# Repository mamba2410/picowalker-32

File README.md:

# picowalker-32

Thsi repo contains all the designs, schematics, pcb layouts and code for the *picowalker-32* project.

The *picowalker-32* is a modern, open source and faithful recreation of the *Pokewalker* from *Pokemon HeartGold/SoulSilver*.
The goal is to have a device that fully mimics the features and functionality of a *Pokewalker*, except made with modern 
features such as a rechargeable battery, colour screen and an additional flash memory chip to store more data.

The *picowalker-32* is based on the STM32U535 chip, which has far more ram, flash and computing capabilities than the original
processor. Most importantly, its available to purchase, even in small quantities.
Due to the lack of options for screens and batteries, the *picowalker-32* is slightly larger than the original *Pokewalker*.

The software in this repo is designed to be enough to run the [picowalker-core]() code to fully simulate a *Pokewalker*,
however, theres no reason that other software can't be run on it!

The name *picowalker-32* comes from the original *picowalker* concept, a [mintyPi](https://sudomod.com/mintypi-v3-5/) inspired
pokewalker, based on the [Raspberry Pi Pico](https://www.raspberrypi.com/products/raspberry-pi-pico/), hence the *pico* in the name.
The project later evolved into a custom-PCB solution using an STM32 controller for lower power draw. Hence the *-32* suffix.

## What's in this repo

- Design files for the schematics and PCB layout, drawn in KiCAD 7.
- STM32CubeMX configuration for the STM32U545 chip used in the design.
- STM32 code using the STM32 HAL for the drivers and dependencies that the [picowalker-core](https://github.com/mamba2410/picowalker-core) needs to function.
- Developer notes and a bill of materials used in testing.
- Other, miscellaneous notes related to the *picowalker-32* project.

## The state of the project

Currently, the project is in active development.
There are schematics, the start of some code and materials that have been picked out.
The project is being prototyped on a breadboard using the *NUCLEO-U545RE* development board and other
breakout boards for fast prototyping.

Left to do:

- Finish the schematics (power delivery, other checks).
- Finish the driver for the screen.
- Start drivers for the IR, accelerometer, eeprom, flash memory, sound, buttons and others.
- Route the PCB (either a test PCB or directly onto the final form factor).
- Manufacture and test the PCB and iterate on it.

## Development and Contribution

If you want to help develop this project, make sure to read the [development document](./development.md) for instructions 
on how to recreate the project at home.

I encourage you to come join the [Discord](https://discord.gg/dVVnM6f5tP)! This is where most of the discussion happens about the project.
There's also other stuff related to the *Pokewalker* including reverse enginnering and hacking it.

Thanks to all the contributors who have helped out a lot, especially

- Kamp, for doing all the CAD work for the shells, picking out components like the screen and battery (which were really hard to find!) and others.
- Zenith, for help with sprites and images and even recreating most of the coloured ones to work on the walker.
- PoroCYon, for help with schematics, electrical questions and picking a suitable MCU.

## Licensing

I'm not sure about the license, I want this project to be as open and accessible as possible.

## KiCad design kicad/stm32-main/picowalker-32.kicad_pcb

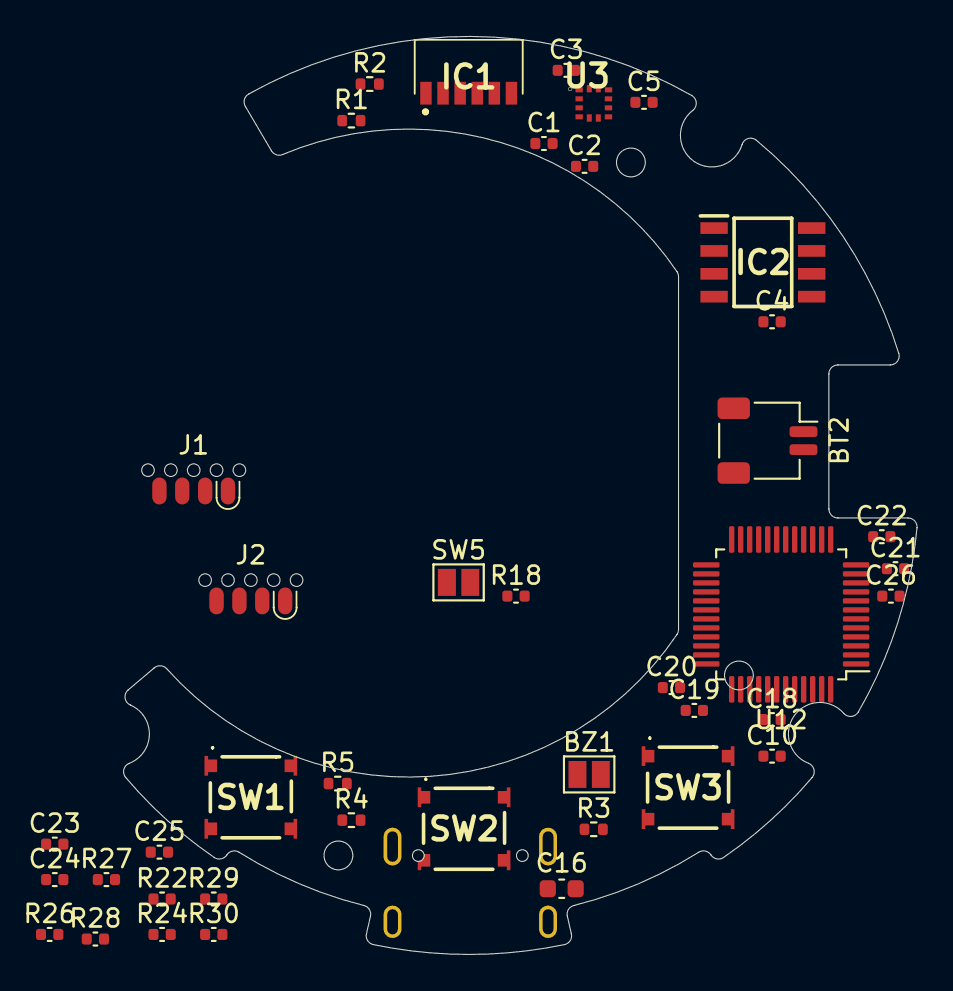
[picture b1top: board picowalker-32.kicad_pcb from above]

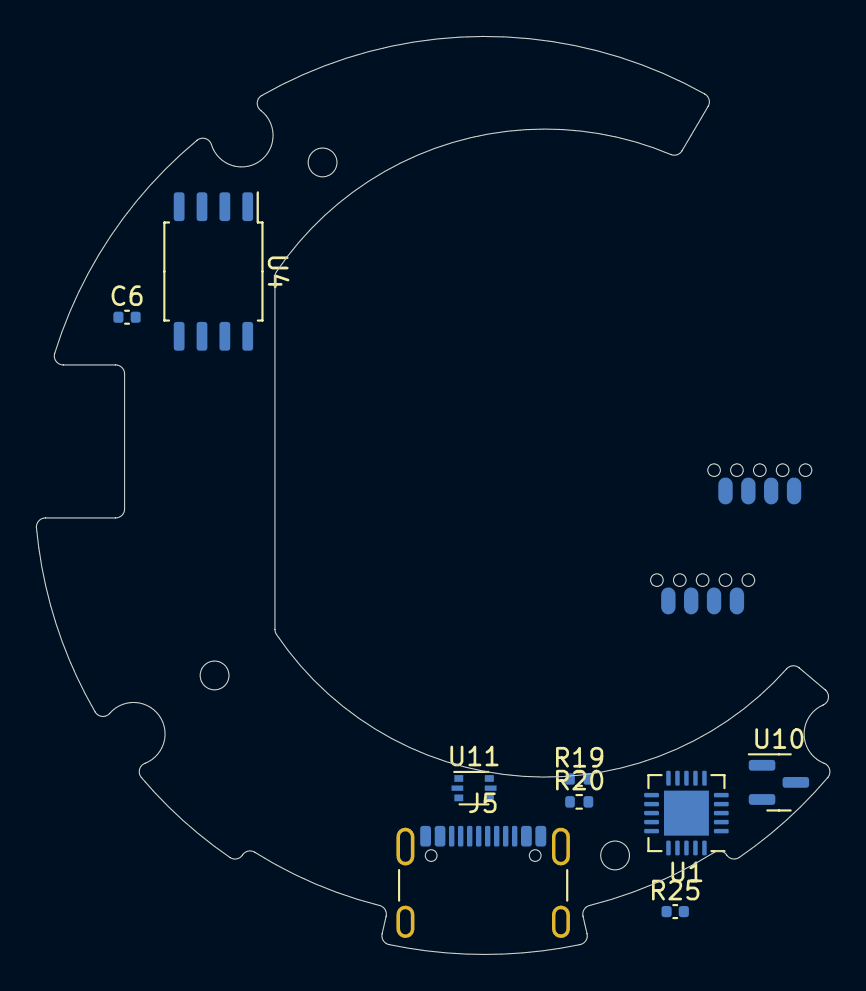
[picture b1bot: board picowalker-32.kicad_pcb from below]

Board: 2 copper layers, 44.1 x 51.0 mm, 50 parts (9 on the bottom side), 47 nets, no tracks yet.

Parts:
BT2: LPR553535A; JST_SH_SM02B-SRSS-TB_1x02-1MP_P1.00mm_Horizontal
BZ1: Speaker; SolderJumper-2_P1.3mm_Open_Pad1.0x1.5mm
C1, C3, C4, C5, C6: 0.1uF; C_0402_1005Metric
C2, C26: 4.7uF; C_0402_1005Metric
C10, C18, C19, C21: 100nF; C_0402_1005Metric
C16: C; C_0603_1608Metric
C20, C23, C24, C25: 10uF; C_0402_1005Metric
C22: 1uF; C_0402_1005Metric
IC1: TFBS4711-TT1; TFBS4711TT1
IC2: M95512-DRMN8TP_K; SOIC127P600X175-8N
J1: DBG_HDR; SOIC_clipProgSmall
J2: PROGRAM_HDR; SOIC_clipProgSmall
J5: USB_C_Receptacle_USB2.0; USB_C_Receptacle_GCT_USB4105-xx-A_16P_TopMnt_Horizontal
R1: 56R; R_0402_1005Metric
R2: 47R; R_0402_1005Metric
R3, R4, R5: 100k; R_0402_1005Metric
R18, R26: 10k; C_0402_1005Metric
R19, R20: 5k1; R_0402_1005Metric
R22, R24, R25: 100k; C_0402_1005Metric
R27: 20k; C_0402_1005Metric
R28: R; C_0402_1005Metric
R29: 330k; C_0402_1005Metric
R30: 110k; C_0402_1005Metric
SW1, SW2, SW3: SW_Push; TL3315NF100Q
SW5: BOOTSEL; SolderJumper-2_P1.3mm_Open_Pad1.0x1.5mm
U1: MCP73871; QFN-20-1EP_4x4mm_P0.5mm_EP2.5x2.5mm
U3: BMA400; BOSCH_LGA-12
U4: W25Q128JVS; SOIC-8_5.23x5.23mm_P1.27mm
U10: MCP1700x-180xxTT; SOT-23
U11: USBLC6-2P6; SOT-666
U12: STM32U535CET6-modified; LQFP-48_7x7mm_P0.5mm

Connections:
+1V8: C10.2, C18.2, C19.2, C20.2, C21.2, C22.2, R22.2, R24.2, R25.2, SW5.1, U10.2 (VO), U12.1 (VBAT), U12.7 (NRST), U12.9 (VDDA), U12.24 (VDD), U12.36 (VDD), U12.48 (VDD)
/power-control-1.8V/BAT+: BT2.1 (+), C23.1, U1.14 (V_{BAT}), U1.15 (V_{BAT}), U1.16 (V_{BAT_SENSE})
/power-control-1.8V/PWR_SRC: C24.2, U1.1 (OUT), U1.20 (OUT), U10.3 (VI)
/power-control-1.8V/USB_5V: C16.1, C25.2, J5.A4 (VBUS), J5.A9 (VBUS), J5.B4 (VBUS), J5.B9 (VBUS), R29.1, U1.9 (~TE), U1.17 (CE), U1.18 (IN), U1.19 (IN), U11.5 (VBUS)
/power-control-1.8V/USB_DN_RAW: J5.A7 (D-), J5.B7 (D-), U11.1 (I/O1)
/power-control-1.8V/USB_DP_RAW: J5.A6 (D+), J5.B6 (D+), U11.3 (I/O2)
/stm32u5/BOOT0: R18.2, SW5.2, U12.44 (PH3-BOOT0)
ACCEL_CSB: J2.7, U3.10 (CSB), U12.41 (PB5)
ACCEL_INT1: U3.5 (INT1), U12.11 (PA1)
BSTAT1: R24.1, U1.8 (STAT1/~LBO), U12.46 (PB9)
BSTAT2: R22.1, U1.7 (STAT2), U12.39 (PB3)
BUT_L: R3.2, SW1.2, U12.2 (PC13)
BUT_M: R4.2, SW2.2, U12.3 (PC14)
BUT_R: R5.2, SW3.2, U12.4 (PC15)
DBG_RX: J1.6, U12.21 (PB10)
DBG_TX: J1.7, U12.12 (PA2)
EEPROM_CSB: IC2.1 (~S), J2.6, U12.29 (PA8)
FLASH_CSB: J2.8, U4.1 (~CS), U12.38 (PA15)
GND: BZ1.2 (+), C1.1, C2.2, C3.2, C4.2, C5.2, C6.2, C10.1, C18.1, C19.1, C20.1, C21.1, C22.1, C26.2, IC1.4 (SD), IC1.6 (GND), IC2.4 (VSS), J1.4, J1.5, J2.1, R18.1, SW1.1, SW2.1, SW3.1, U3.8 (GNDIO), U3.9 (GND), U4.4 (GND), U12.8 (VSSA), U12.23 (VSS), U12.35 (VSS), U12.47 (VSS)
GNDPWR: BT2.2 (-), C16.2, C23.2, C24.1, C25.1, J5.A1 (GND), J5.A12 (GND), J5.B1 (GND), J5.B12 (GND), J5.S1 (SHIELD), R19.2, R20.2, R26.1, R27.2, R28.2, R30.2, U1.3 (SEL), U1.4 (PROG2), U1.10 (V_{SS}), U1.11 (V_{SS}), U1.21 (V_{SS}), U10.1 (GND), U11.2 (GND)
MISO: IC2.2 (Q), J2.2, U3.1 (SDO), U12.27 (PB14)
MOSI: IC2.5 (D), J2.3, U3.2 (SDX), U12.28 (PB15)
unnamed: C1.2, IC1.5 (VCC1), R2.2
unnamed: C2.1, IC1.1 (VCC2/IRED/ANODE), R1.1
unnamed: J5.A5 (CC1), R19.1
unnamed: J5.B5 (CC2), R20.1
unnamed: R27.1, U1.13 (PROG1)
unnamed: R28.1, U1.12 (PROG3)
unnamed: R26.2, U1.5 (THERM)
unnamed: R29.2, R30.1, U1.2 (VPCC)
unnamed: C26.1, U12.22 (VCAP)
PWR: C3.1, C4.1, C5.1, C6.1, IC2.3 (~W), IC2.7 (~HOLD), IC2.8 (VCC), R1.2, R2.1, R3.1, R4.1, R5.1, U3.3 (VDDIO), U3.7 (VDD), U4.8 (VCC)
QSCK: U4.6 (CLK), U12.13 (PA3)
QSPI0: U4.5 (DI(IO0)), U12.19 (PB1)
QSPI1: U4.2 (DO(IO1)), U12.18 (PB0)
QSPI2: U4.3 (IO2), U12.17 (PA7)
QSPI3: U4.7 (IO3), U12.16 (PA6)
RXDIR: IC1.3 (RXD), U12.31 (PA10)
SCK: IC2.6 (C), J2.4, U3.12 (SCX), U12.26 (PB13)
SCREEN_CSB: J2.5, U12.14 (PA4)
SOUND_SRC: BZ1.1 (-), U12.15 (PA5)
SWCLK: J1.2, U12.37 (PA14)
SWDIO: J1.3, U12.34 (PA13)
TXDIR: IC1.2 (TXD), U12.30 (PA9)
USB_DN: U11.6 (I/O1), U12.32 (PA11)
USB_DP: U11.4 (I/O2), U12.33 (PA12)
~PG: R25.1, U1.6 (~PG), U12.45 (PB8)

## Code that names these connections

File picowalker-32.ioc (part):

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Mcu.Name=STM32U535CETx
Mcu.Package=LQFP48
Mcu.UserName=STM32U535CETx
PA0.Mode=WakeUp1
PA0.Signal=PWR_WKUP1
PA1.GPIOParameters=GPIO_Label
PA1.GPIO_Label=ACCEL_INT1
PA1.Signal=GPIO_Input
PA10.GPIOParameters=GPIO_Label
PA10.GPIO_Label=IrDA_RX
PA10.Mode=IrDA
PA10.Signal=USART1_RX
PA11.Mode=Device
PA11.Signal=USB_DM
PA12.Mode=Device
PA12.Signal=USB_DP
PA13\ (JTMS/SWDIO).Mode=Serial_Wire
PA13\ (JTMS/SWDIO).Signal=DEBUG_JTMS-SWDIO
PA14\ (JTCK/SWCLK).Mode=Serial_Wire
PA14\ (JTCK/SWCLK).Signal=DEBUG_JTCK-SWCLK
PA15\ (JTDI).GPIOParameters=GPIO_Label
PA15\ (JTDI).GPIO_Label=FLASH_CSB
PA15\ (JTDI).Signal=GPIO_Output
PA2.GPIOParameters=GPIO_Label
PA2.GPIO_Label=DBG_TX
PA2.Mode=Asynchronous
PA2.Signal=LPUART1_TX
PA3.GPIOParameters=GPIO_PuPd
PA3.GPIO_PuPd=GPIO_PULLUP
PA3.Mode=quad_mode
PA3.Signal=OCTOSPI1_CLK
PA4.GPIOParameters=GPIO_PuPd
PA4.GPIO_PuPd=GPIO_PULLUP
PA4.Mode=quad_mode
PA4.Signal=OCTOSPI1_NCS
PA5.GPIOParameters=GPIO_Label
PA5.GPIO_Label=SPKR_DAC
PA5.Signal=COMP_DAC12_group
PA6.GPIOParameters=GPIO_PuPd,GPIO_Speed_High_Default,GPIO_Mode
PA6.GPIO_Mode=GPIO_MODE_AF_PP
PA6.GPIO_PuPd=GPIO_NOPULL
PA6.GPIO_Speed_High_Default=GPIO_SPEED_FREQ_VERY_HIGH
PA6.Mode=quad_mode
PA6.Signal=OCTOSPI1_IO3
PA7.GPIOParameters=GPIO_PuPd,GPIO_Speed_High_Default,GPIO_Mode
PA7.GPIO_Mode=GPIO_MODE_AF_PP
PA7.GPIO_PuPd=GPIO_NOPULL
PA7.GPIO_Speed_High_Default=GPIO_SPEED_FREQ_VERY_HIGH
PA7.Mode=quad_mode
PA7.Signal=OCTOSPI1_IO2
PA8.GPIOParameters=GPIO_Label
PA8.GPIO_Label=EEPROM_CSB
PA8.Signal=GPIO_Output
PA9.GPIOParameters=GPIO_Label
PA9.GPIO_Label=IrDA_TX
PA9.Mode=IrDA
PA9.Signal=USART1_TX
PB0.GPIOParameters=GPIO_PuPd,GPIO_Speed_High_Default,GPIO_Mode
PB0.GPIO_Mode=GPIO_MODE_AF_PP
PB0.GPIO_PuPd=GPIO_NOPULL
PB0.GPIO_Speed_High_Default=GPIO_SPEED_FREQ_VERY_HIGH
PB0.Mode=quad_mode
PB0.Signal=OCTOSPI1_IO1
PB1.GPIOParameters=GPIO_PuPd,GPIO_Speed_High_Default,GPIO_Mode
PB1.GPIO_Mode=GPIO_MODE_AF_PP
PB1.GPIO_PuPd=GPIO_NOPULL
PB1.GPIO_Speed_High_Default=GPIO_SPEED_FREQ_VERY_HIGH
PB1.Mode=quad_mode
PB1.Signal=OCTOSPI1_IO0
PB10.GPIOParameters=GPIO_Label
PB10.GPIO_Label=DBG_RX
PB10.Mode=Asynchronous
PB10.Signal=LPUART1_RX
PB12.GPIOParameters=GPIO_Label
PB12.GPIO_Label=TP_INT
PB12.Signal=GPIO_Input
PB13.GPIOParameters=GPIO_PuPd
PB13.GPIO_PuPd=GPIO_PULLUP
PB13.Mode=Full_Duplex_Master
PB13.Signal=SPI2_SCK
PB14.Mode=Full_Duplex_Master
PB14.Signal=SPI2_MISO
PB15.Mode=Full_Duplex_Master
PB15.Signal=SPI2_MOSI
PB2.GPIOParameters=GPIO_Label
PB2.GPIO_Label=SCREEN_RST
PB2.Signal=GPIO_Output
PB3\ (JTDO/TRACESWO).GPIOParameters=GPIO_Label
PB3\ (JTDO/TRACESWO).GPIO_Label=BSTAT2
PB3\ (JTDO/TRACESWO).Signal=GPIO_Input
PB4\ (NJTRST).Mode=INP
PB4\ (NJTRST).Signal=COMP1_INP
PB5.GPIOParameters=GPIO_Label
PB5.GPIO_Label=ACCEL_CSB
PB5.Signal=GPIO_Output
PB6.Mode=I2C
PB6.Signal=I2C1_SCL
PB7.Mode=I2C
PB7.Signal=I2C1_SDA
PB8.GPIOParameters=GPIO_Label
PB8.GPIO_Label=PGB
PB8.Signal=GPIO_Input
PB9.GPIOParameters=GPIO_Label
PB9.GPIO_Label=BSTAT1
PB9.Signal=GPIO_Input
PC13.GPIOParameters=GPIO_Label
PC13.GPIO_Label=BUT1
PC13.Signal=GPIO_Input
PC14-OSC32_IN\ (PC14).GPIOParameters=GPIO_Label
PC14-OSC32_IN\ (PC14).GPIO_Label=BUT2
PC14-OSC32_IN\ (PC14).Signal=GPIO_Input
PC15-OSC32_OUT\ (PC15).GPIOParameters=GPIO_Label
PC15-OSC32_OUT\ (PC15).GPIO_Label=BUT3
PC15-OSC32_OUT\ (PC15).Signal=GPIO_Input
PH3-BOOT0.GPIOParameters=GPIO_Label
PH3-BOOT0.GPIO_Label=BOOT0
PH3-BOOT0.Signal=GPIO_Input
RCC.HSE_VALUE=16000000
board=custom

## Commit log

2024-04-13 Add kicad files
2024-04-13 Add CubeMX and other source files
2024-04-13 Add todos
2024-04-13 Update schematic and add basic PCB layout
2024-04-13 Update hardware todo
2024-04-13 Add nucleo/bare cubemx files
2024-04-13 Change schematic MCU pinouts
2024-04-18 add rest of screen functions, not tested
2024-04-18 move transform to function and rename others
2024-04-18 Add accelerometer code
2024-04-18 oops, accel in the wrong folder
2024-04-18 fix mega typo in function call
2024-04-18 add code for 25lc512 eeprom
2024-04-18 add accelerometer functions to picowalker-defs.h
2024-04-18 progress on ir code, missing timers
2024-04-18 make a start on flash spi code
2024-04-19 investigating hardware voltages and sleep mode
2024-04-19 comments about power, changed eeprom and flash packages
2024-04-19 added chip package to todo
2024-04-21 playing with battery/power circuit
2024-05-25 fix screen compiler errors
2024-05-25 fix screen transform
2024-05-25 change target to picowalker-32-nucleo
2024-05-26 set uart4 to uart mode for irda 3 click
2024-05-26 lower ospi fifo threshold, increase clock speed
2024-05-26 update todo
2024-05-26 specify stm32cubemx version
2024-05-26 add logging
2024-05-26 eeprom spi works at 1MHz, need to fix 1ms delays
2024-05-26 spi works properly with accel and eeprom
2024-05-27 added IR code, transmit broken
2024-05-27 add button interrupt code
2024-05-27 update gitignore
2024-05-27 buttons now actually call picowalker-core callback
2024-05-27 add log for when accel chipid check fails
2024-05-27 remove delay in screen draw function
2024-05-27 modify to run picowalker-core
2024-05-27 fix draw_text_box primitive
2024-05-27 add accel int pin
2024-07-21 hw: change to 3v3 LDO and remove unnecessary MCU pins
2024-07-21 hw: update power symbols, clean up some power circuitry
2024-07-21 hw: more consideration on battery circuit
2024-08-12 hw: change battery to a "simpler" version
2024-08-17 hw: moved main design into sub folder
2024-08-17 hw: pico2 carrier board quick schematic
2024-08-18 hw: screen updates
2024-08-26 hw: update screen stuff
2024-08-26 hw: add bq25628e rough design
2024-08-26 hw: lots of changes to pico 2 board
